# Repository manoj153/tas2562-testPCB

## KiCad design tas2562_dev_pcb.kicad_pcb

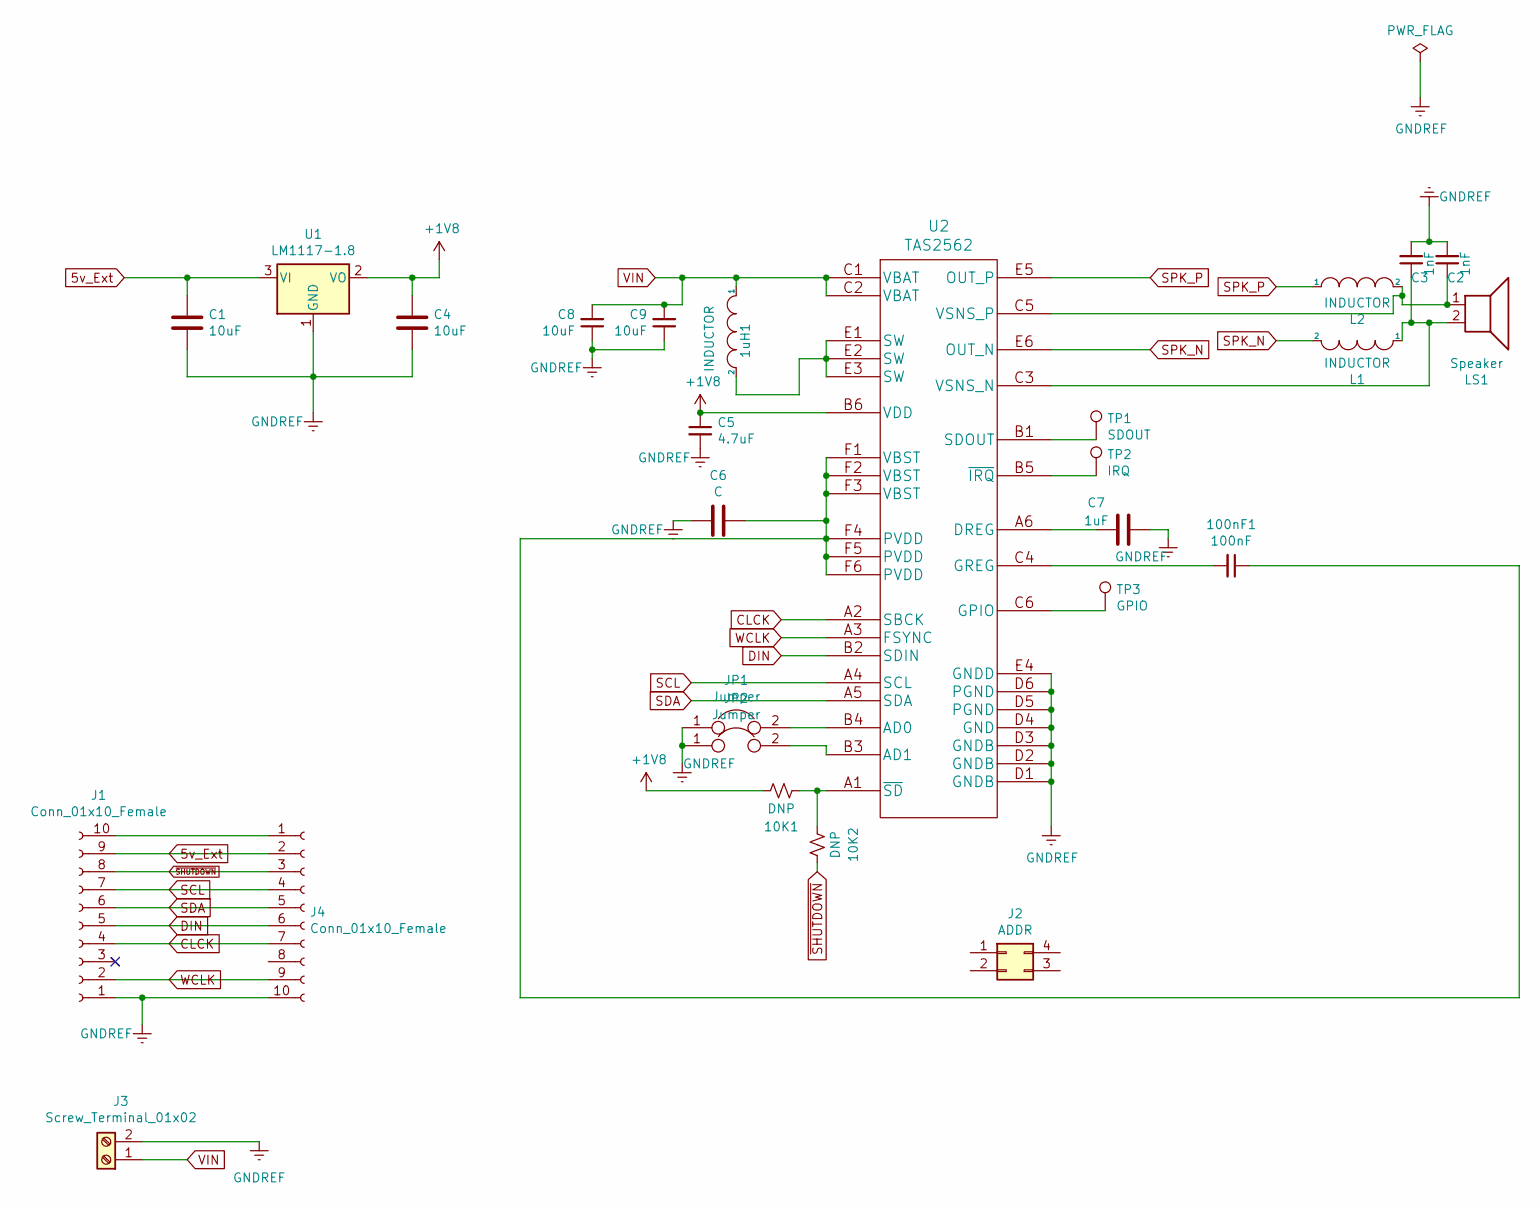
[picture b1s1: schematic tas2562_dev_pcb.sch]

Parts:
1uH1: INDUCTOR; 6.6-6.4
10K1, 10K2: DNP; R_0805_2012Metric
100nF1: 100nF; C_0805_2012Metric
C1, C4, C8, C9: 10uF; C_0805_2012Metric
C2, C3: 1nF; C_0805_2012Metric
C5: 4.7uF; C_0805_2012Metric
C6: C; C_0805_2012Metric
C7: 1uF; C_0805_2012Metric
J1, J4: Conn_01x10_Female; PinHeader_1x10_P2.54mm_Vertical
J2: ADDR; PinHeader_2x02_P2.54mm_Vertical
J3: Screw_Terminal_01x02; TerminalBlock_bornier-2_P5.08mm
JP1, JP2: Jumper; SolderJumper-2_P1.3mm_Open_TrianglePad1.0x1.5mm
L1, L2: INDUCTOR; L_0805_2012Metric
LS1: Speaker; TerminalBlock_bornier-2_P5.08mm
TP1: SDOUT; TestPoint_Pad_D1.5mm
TP2: IRQ; TestPoint_Pad_D1.5mm
TP3: GPIO; TestPoint_Pad_D1.5mm
U1: LM1117-1.8; SOT-223
U2: TAS2562; bga36tas

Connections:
5v_Ext: C1.1, J1.9, J4.2, U1.3 (VI)
+1V8: 10K1.2, C4.1, C5.1, U1.2 (VO), U2.B6 (VDD)
CLCK: J1.4, J4.7, U2.A2 (SBCK)
DIN: J1.5, J4.6, U2.B2 (SDIN)
GNDREF: C1.2, C2.2, C3.2, C4.2, C5.2, C6.2, C7.1, C8.1, C9.1, J1.1, J3.2, J4.10, JP1.1, JP2.1, U1.1 (GND), U2.D1 (GNDB), U2.D2 (GNDB), U2.D3 (GNDB), U2.D4 (GND), U2.D5 (PGND), U2.D6 (PGND), U2.E4 (GNDD)
unnamed: 1uH1.2, U2.E1 (SW), U2.E2 (SW), U2.E3 (SW)
unnamed: 10K1.1, 10K2.1, U2.A1 (~SD)
unnamed 7: 100nF1.1, C6.1, U2.F1 (VBST), U2.F2 (VBST), U2.F3 (VBST), U2.F4 (PVDD), U2.F5 (PVDD), U2.F6 (PVDD); also elsewhere on the board
unnamed 8: 100nF1.2, U2.C4 (GREG); also elsewhere on the board
unnamed: C2.1, L2.2, LS1.1, U2.C5 (VSNS_P)
unnamed: C3.1, L1.1, LS1.2, U2.C3 (VSNS_N)
unnamed: C7.2, U2.A6 (DREG)
unnamed: J1.10, J4.1
unnamed: JP1.2, U2.B4 (AD0)
unnamed: JP2.2, U2.B3 (AD1)
unnamed: TP1.1, U2.B1 (SDOUT)
unnamed: TP2.1, U2.B5 (~IRQ)
unnamed: TP3.1, U2.C6 (GPIO)
SCL: J1.7, J4.4, U2.A4 (SCL)
SDA: J1.6, J4.5, U2.A5 (SDA)
SPK_N: L1.2, U2.E6 (OUT_N)
SPK_P: L2.1, U2.E5 (OUT_P)
VIN: 1uH1.1, C8.2, C9.2, J3.1, U2.C1 (VBAT), U2.C2 (VBAT)
WCLK: J1.2, J4.9, U2.A3 (FSYNC)
~SHUTDOWN: 10K2.2, J1.8, J4.3

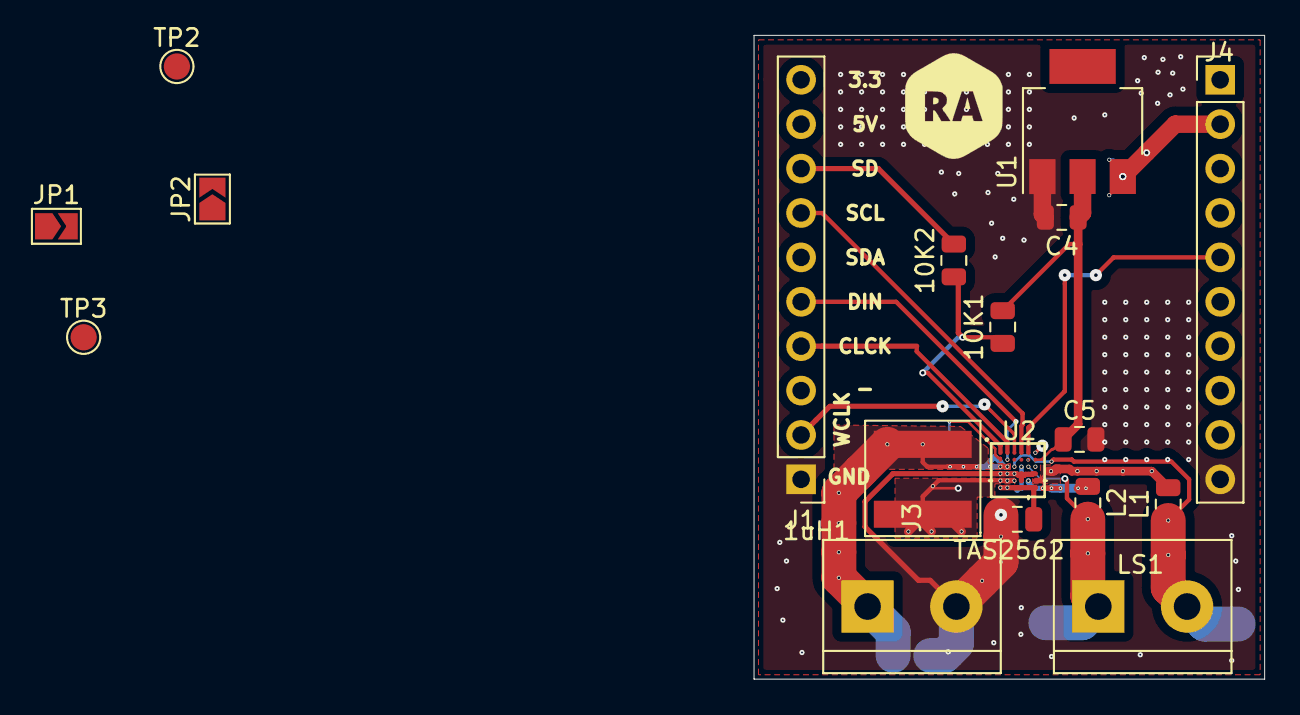
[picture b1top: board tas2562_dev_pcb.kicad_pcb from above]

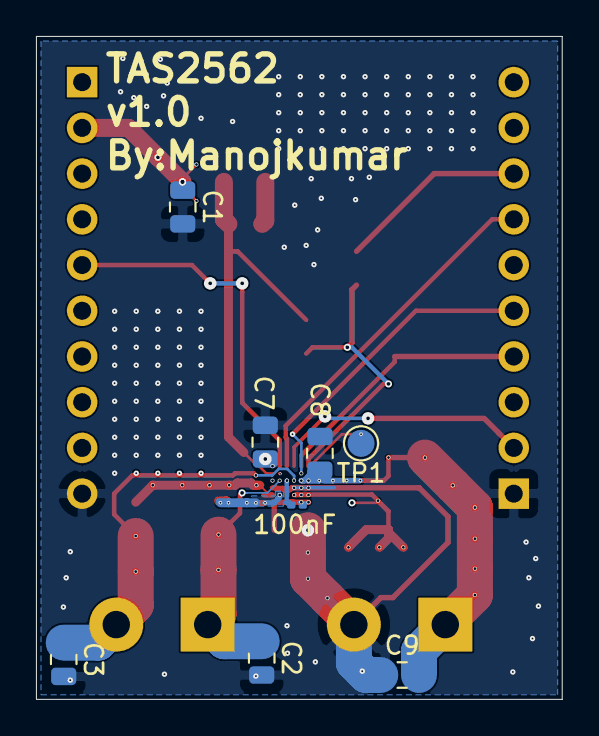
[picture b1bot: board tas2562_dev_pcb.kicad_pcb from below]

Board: 2 copper layers, 29.2 x 36.8 mm, 26 parts (8 on the bottom side), 25 nets.

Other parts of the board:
100nF: 100nF; C_0201_0603Metric

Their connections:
unnamed 7: 100nF.1; also elsewhere on the board
unnamed 8: 100nF.2; also elsewhere on the board

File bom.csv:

Reference, Value, Footprint, Datasheet
"LS1","Speaker","TerminalBlock:TerminalBlock_bornier-2_P5.08mm","~"
"L1","INDUCTOR","Inductor_SMD:L_0805_2012Metric","~"
"L2","INDUCTOR","Inductor_SMD:L_0805_2012Metric","~"
"C2","1nF","Capacitor_SMD:C_0805_2012Metric","~"
"C3","1nF","Capacitor_SMD:C_0805_2012Metric","~"
"U2","TAS2562","tas2562_dev_pcb:bga36tas",""
"1uH1","INDUCTOR","Inductor_SMD:6.6-6.4","~"
"U1","LM1117-1.8","Package_TO_SOT_SMD:SOT-223","http://www.ti.com/lit/ds/symlink/lm1117.pdf"
"C1","10uF","Capacitor_SMD:C_0805_2012Metric","~"
"C4","10uF","Capacitor_SMD:C_0805_2012Metric","~"
"C5","4.7uF","Capacitor_SMD:C_0805_2012Metric","~"
"C6","C","Capacitor_SMD:C_0805_2012Metric","~"
"J2","ADDR","Connector_PinHeader_2.54mm:PinHeader_2x02_P2.54mm_Vertical","~"
"100nF1","100nF","Capacitor_SMD:C_0805_2012Metric","~"
"10K1","DNP","Resistor_SMD:R_0805_2012Metric","~"
"C7","1uF","Capacitor_SMD:C_0805_2012Metric","~"
"TP1","SDOUT","TestPoint:TestPoint_Pad_D1.5mm","~"
"TP3","GPIO","TestPoint:TestPoint_Pad_D1.5mm","~"
"TP2","IRQ","TestPoint:TestPoint_Pad_D1.5mm","~"
"J1","Conn_01x10_Female","Connector_PinHeader_2.54mm:PinHeader_1x10_P2.54mm_Vertical","~"
"10K2","DNP","Resistor_SMD:R_0805_2012Metric","~"
"J3","Screw_Terminal_01x02","TerminalBlock:TerminalBlock_bornier-2_P5.08mm","~"
"J4","Conn_01x10_Female","Connector_PinHeader_2.54mm:PinHeader_1x10_P2.54mm_Vertical","~"
"C8","10uF","Capacitor_SMD:C_0805_2012Metric","~"
"JP1","Jumper","Jumper:SolderJumper-2_P1.3mm_Open_TrianglePad1.0x1.5mm","~"
"JP2","Jumper","Jumper:SolderJumper-2_P1.3mm_Open_TrianglePad1.0x1.5mm","~"
"C9","10uF","Capacitor_SMD:C_0805_2012Metric","~"

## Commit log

2019-05-26 first commit wih 4 layer done but trying for 2 layer now
2019-05-26 added gerber, layout done in 2layers
